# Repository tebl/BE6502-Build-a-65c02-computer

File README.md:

# BE6502 - Build a 6502 computer
[Ben Eater](https://eater.net/) has been a huge inspiration for many getting into building computers using basic electronic building blocks, his [videos](https://www.youtube.com/user/eaterbc) are truly excellent and it is no wonder he's often referred to as the Bob Ross of Breadboards! His latest project is [building a 6502 computer](https://eater.net/6502) on a breadboard, a video series that at this moment in time still has not concluded so this may not match whatever he does after part 7!

Personally, I am somewhat awful at getting things to work on breadboards - even when buying the good stuff from reputable electronics shops, so I usually just go directly to PCB instead. I've designed a few other amateur projects using the trusty old 6502-processor before, but this'll be the first one to be tackled with the more modern Western Designs CPU (W65C02) instead. His video series depends this specific brand of CPU, this is due to the way it is run using a slow and sometimes completely halted clock that wouldn't work the same on other brands. The older 6502 variants will more than likely loose their context, with the end result being a CPU doing unexpected things instead of running as the machine code would normally dictate. 

![LCD mounted](https://github.com/tebl/BE6502/raw/master/gallery/2019-12-06%2019.39.01.jpg
)

The BE6502 computer has a 39-pin backplane connector, like most of my other projects and these can be used to connect to an Arduino Mega as in the videos, a logic probe or even a separate larger backplane if you intend to build any more additional expansions for use with the computer. The picture above shows the SBC along with clock and Arduino Mega Shield. See *System modules* below for a listing of available modules, which are required at the various steps in the video series and any optional extras I felt like listing that would be compatible with the supplied boards.

Over time I may even add some short videos to show off the computer in action, but given that I have a voice suited for silent movies they'll probably just be videos of the computer blinking away by itself. As they become available, you'll find those on this [Youtube-playlist](https://www.youtube.com/playlist?list=PLOJSxpeHB9KTk9ptKCbEZnNEy9QRU02SS).

## Project status
The BE6502 computer is still in the prototyping stage and though I have studied the videos up to this point, at the time of writing that'd be everything up to and including part 7. See [TODO](https://github.com/tebl/BE6502/blob/master/TODO.md) for an overview of things I've yet to implement or want to change in the future!

Some of these details are likely to change as his original design by itself does not seem to reset reliably when using the 1 Mhz clock. At the moment I've got it fixed by using one of my own RC6502-modules in one of the backplane slots, details for this module can be found at https://github.com/tebl/RC6502-Apple-1-Replica/tree/master/RC6502%20Reset%20Circuit. If you'd like to build it up on a breadboard you can easily do that, I've installed pin headers as the front slot of my backplane to make it easier to do things like that. Alternatively you could program the Arduino Mega to do it for you!

### Errata
* [BE6502 SBC](https://github.com/tebl/BE6502/tree/master/BE6502%20SBC) revision A boards are missing a pull-up on the BE-pin - refer to this [picture](https://github.com/tebl/BE6502-Build-a-65c02-computer/raw/master/gallery/2020-02-16%2015.50.14-1.jpg) for a convenient spot to add one. This is resistor R18 in the current version of the schematic.
* [BE6502 Clock](https://github.com/tebl/BE6502-Build-a-65c02-computer/tree/master/BE6502%20Clock) module revision B had C8 shorted, refer to this [picture](https://github.com/tebl/BE6502-Build-a-65c02-computer/blob/master/gallery/Screenshot%202021-11-30%20194604.png) for how it should have looked (tracks have not been moved). In order to fix an existing PCB, cut off C8 and cut the trace directly below it. Installing new C8 (100nF) can be done on the back of the board, either across the short side of SW1 or between U2 pins 1 and 2.

## System modules
The following listed modules are available for use with the computer, where available I've also added an order URL to a shared project on PCBway for ease of ordering - click the module name to get more information as well as a complete list of components needed to build it (usually referred to as a BOM). Some modules have been marked with other computer names, these are other modules that I've found works directly and can be of interest when playing around with the BE6502-computer.

| Name      | Video series, parts 1-7 | Future expansions | Order  |
| --------- | ----------------------- | ----------------- | ------ |
| [Computer (SBC)](https://github.com/tebl/BE6502/tree/master/BE6502%20SBC) | required | | [PCBway](https://www.pcbway.com/project/shareproject/BE6502_Build_a_6502_computer__SBC_module_revision_A_.html?inviteid=88707) |
| [Adjustable and manual clock](https://github.com/tebl/BE6502/tree/master/BE6502%20Clock) | required | | [PCBway](https://www.pcbway.com/project/shareproject/BE6502_Build_a_6502_computer__Clock_module_revision_A_.html?inviteid=88707) |
| [Arduino Mega Shield and Backplane ](https://github.com/tebl/BE6502/tree/master/BE6502%20Mega%20Adapter) | required | | [PCBway](https://www.pcbway.com/project/shareproject/BE6502_Build_a_6502_computer__Arduino__and_backplane_module_.html?inviteid=88707) |
| [RC6502 Backplane](https://github.com/tebl/RC6502-Apple-1-Replica/tree/master/RC6502%20Backplane) |  | optional | [PCBWay](https://www.pcbway.com/project/shareproject/RC6502_Apple_1_Replica__Backplane_module_revision_A_.html?inviteid=88707) |
| [RC6502 Prototyping module](https://github.com/tebl/RC6502-Apple-1-Replica/tree/master/RC6502%20Prototyping) | | optional | [PCBWay](https://www.pcbway.com/project/shareproject/RC6502_Apple_1_Replica__Module_prototyping_board_.html?inviteid=88707) |

If you would like to have a copy of one or more modules (usually 5$ per module), consider using the order links in order to support the development of these boards while doing so. You can alternatively zip up the contents of the export directory for each module and give that to your favourite PCB fabrication plant instead if you want to, but note that the files online here may be newer and have changes made to them that may not have been tested yet (the order link above will point to my last tested version).

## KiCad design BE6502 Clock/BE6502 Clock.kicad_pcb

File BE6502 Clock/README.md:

[Ben Eater](https://eater.net/) has been a huge inspiration for many getting into building computers using basic electronic building blocks, his [videos](https://www.youtube.com/user/eaterbc) are truly excellent and it is no wonder he's often referred to as the Bob Ross of Breadboards! His latest project is [building a 6502 computer](https://eater.net/6502) on a breadboard, a video series that I'm sure will also inspire a lot of new users to the art of building stuff with the 6502! Check out the main [README](https://github.com/tebl/BE6502) for an overview of all the modules available to the BE6502 computer.

## Clock Module
Ben Eater has used the clock module from his 8 bit computer build with this project as well, this module is my implementation with only a few tweaks to the design. The main change apart from the whole PCB-design is that it has a slightly reduced chip-count, this was done by replacing the single used OR-gate with three NAND-gates instead (a little NAND-logic exercise).

Like the original breadboard version, you have a manual clock that allows you to clock in manual clock-pulses by pushing the button - the 555 in this case is used for debouncing (mechanical switches are not actually all that consistent). An adjustable slow clock is also available, here the 555 is used as a vibrator and will generate clock pulses with a frequency that is adjustable via the potentiometer. The final 555 allows for a clean transition between the two clocks so you can switch between the two without any erratic bahavior.

# Schematic
The supplied KiCad files should be sufficient as both a schematic and as a starting point for ordering PCBs (basically you could just zip the contents of the export folder and upload that on a fabrication site), the schematic is also available in [PDF-format](https://github.com/tebl/BE6502/raw/master/BE6502%20Clock/export/BE6502%20Clock.pdf) so that you can refer to it while troubleshooting. You could even print it out and hang it on your office wall, excellent conversation starter at any technology-oriented business worth working at (or so I keep telling myself)!

# BOM
This is the part list as it stands now, most should be easy to get a hold of from your local electronic component shop though you might have to consider other sources depending on the quality of yourlocal vendor.

Some vendors will have the same ICs in different form factors, the ones you want will often be specified as being in the form of a DIP/PDIP package. Usually you'll want sockets for each of the ICs as well, a bag of assorted sockets should be easily available without setting you back more than a couple bucks. With the sockets in place, you don't need to dread having to remove an IC later, this leads to easier fault finding and you can easily "borrow" them for other projects later! For the pin headers; if you can't find the exact pin count, just buy the longer 40 pin versions and snip off the parts you don't need.

| Reference    | Item                                  | Count |
| ------------ | ------------------------------------- | ----- |
| PCB          | Fabricate yourself using Gerber files ([order](https://www.pcbway.com/project/shareproject/BE6502_Build_a_6502_computer__Clock_module_revision_A_.html?inviteid=88707)) |     1 |
| C1.C2,C5     | 10nF ceramic capacitor                |     3 |
| C3.C4,C7     | 100nF ceramic capacitor               |     3 |
| C6           | 1uF electrolytic capacitor (2.5mm)    |     1 |
| D1           | 5mm LED                               |     1 |
| R1-R3,R5-R6  | 1k ohm resistor                       |     5 |
| R4           | 1M ohm resistor                       |     1 |
| R7           | 220 ohm resistor                      |     1 |
| RV1          | Bourns 3296W 1M ohm potentiometer     |     1 |
| U1-U3        | LM555, NE555 or equivalent (DIP-8)    |     3 |
| U4           | 74HC00 (DIP-14) *                     |     1 |
| U5           | 74HC08 (DIP-14) *                     |     1 |
| SW1          | Momentary push button                 |     1 |
| SW2          | 6pin 8.5mm x 8.5mm latching switch    |     1 |
| J1           | 4p straight pin header **             |     1 |

\*) HC-series chips have been specified as that is what Ben Eater used in his Build a 6502 computer series, but can also be HCT-series depending on what you have access to. For more information on the various logic families, see the [6502 Primer on the topic of logic families](http://wilsonminesco.com/6502primer/LogicFamilies.html).

\**) You can use a female right-angle pin header and match it directly to the BE6502 SBC with some careful adjustments, but I recommend using some female to female dupont leads instead as the connector is a bit too loose when not mounting boards on a backing plate.

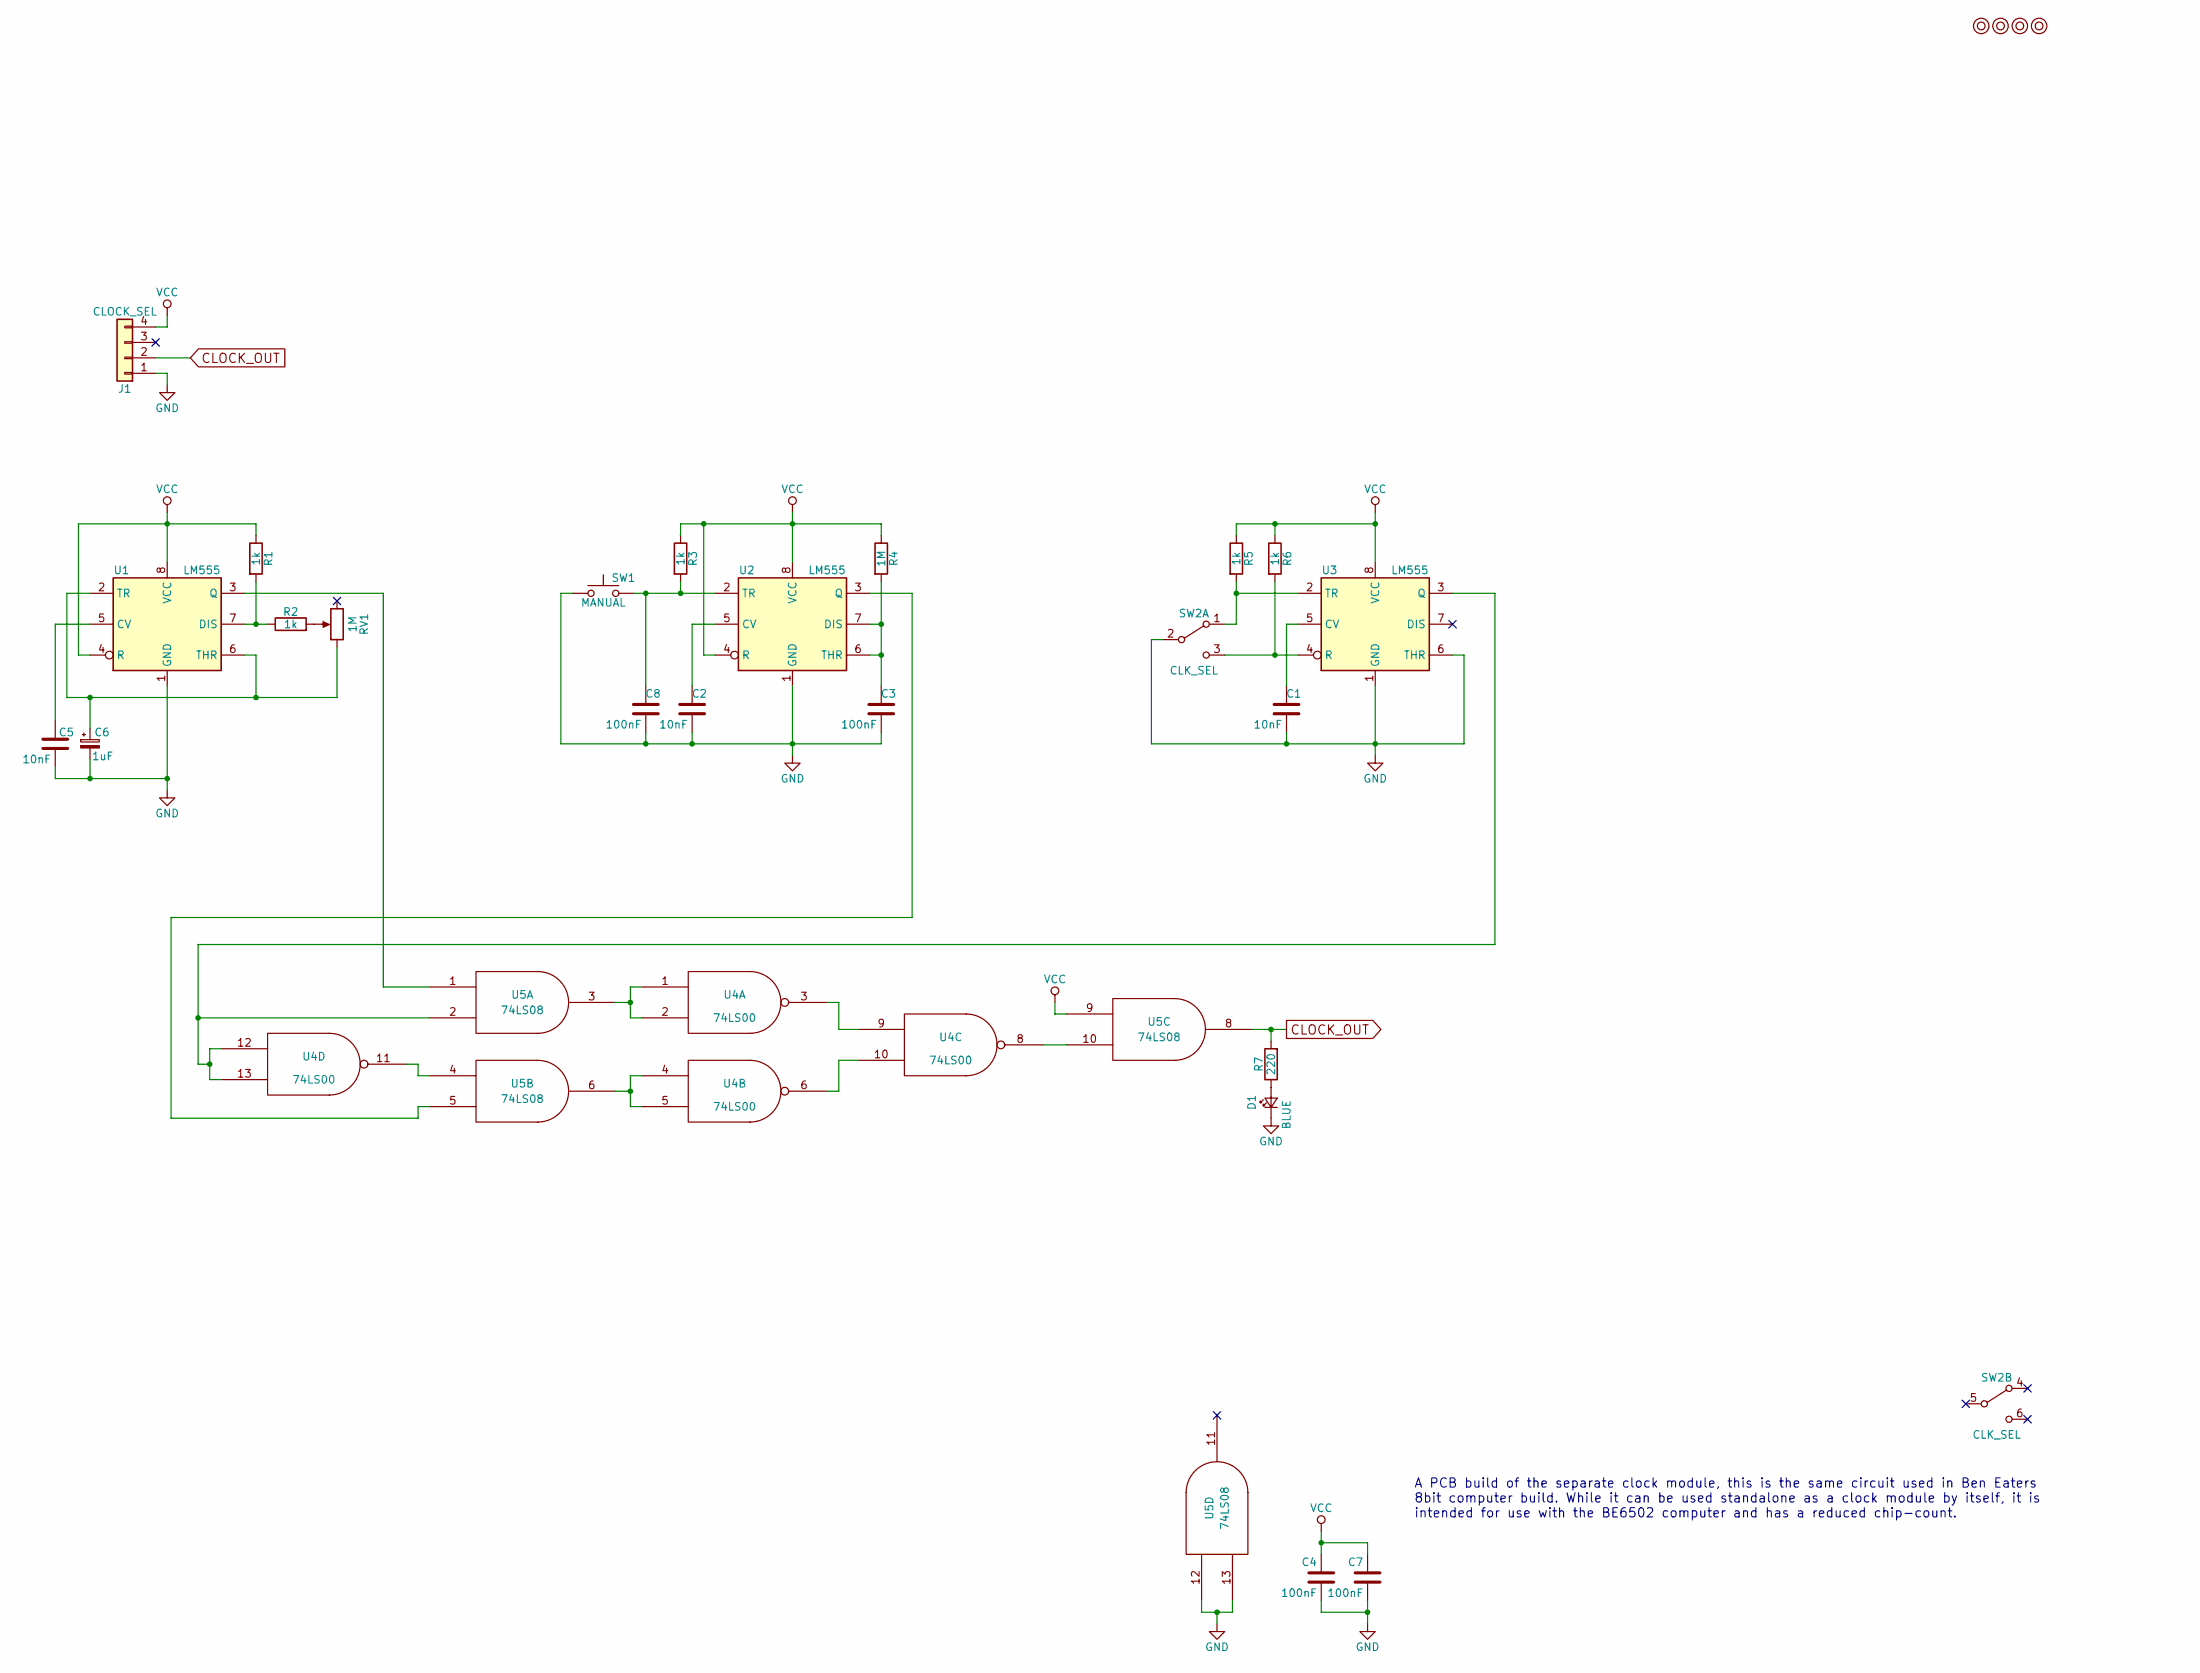
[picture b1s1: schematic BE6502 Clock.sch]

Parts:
C1, C2, C5: 10nF; C_Disc_D4.7mm_W2.5mm_P5.00mm
C3, C4, C7, C8: 100nF; C_Disc_D4.7mm_W2.5mm_P5.00mm
C6: 1uF; CP_Radial_D4.0mm_P2.00mm
D1: BLUE; LED_D5.0mm
J1: CLOCK_SEL; Pin_Header_Angled_1x04_Pitch2.54mm
M1, M2, M3, M4: Mounting; 1pin
R1, R2, R3, R5, R6: 1k; R_Axial_DIN0207_L6.3mm_D2.5mm_P10.16mm_Horizontal
R4: 1M; R_Axial_DIN0207_L6.3mm_D2.5mm_P10.16mm_Horizontal
R7: 220; R_Axial_DIN0207_L6.3mm_D2.5mm_P10.16mm_Horizontal
RV1: 1M; Potentiometer_Trimmer_Bourns_3296W
SW1: MANUAL; SW_PUSH_6mm
SW2: CLK_SEL; dpdt_switch
U1, U2, U3: LM555; DIP-8_W7.62mm_Socket_LongPads
U4: 74LS00; DIP-14_W7.62mm_Socket_LongPads
U5: 74LS08; DIP-14_W7.62mm_Socket_LongPads

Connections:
CLOCK_OUT: J1.2, R7.2, U5.8
GND: C1.2, C2.2, C3.2, C4.2, C5.2, C6.2, C7.2, C8.2, D1.1 (K), J1.1, SW1.1, SW2.2 (B), U1.1 (GND), U2.1 (GND), U3.1 (GND), U3.6 (THR), U4.7 (GND), U5.7 (GND), U5.12, U5.13
unnamed: C1.1, U3.5 (CV)
unnamed: C2.1, U2.5 (CV)
unnamed: C3.1, R4.2, U2.6 (THR), U2.7 (DIS)
unnamed: C5.1, U1.5 (CV)
unnamed: C6.1, RV1.1, U1.2 (TR), U1.6 (THR)
unnamed: C8.1, R3.2, SW1.2, U2.2 (TR)
unnamed: D1.2 (A), R7.1
unnamed: R1.2, R2.1, U1.7 (DIS)
unnamed: R2.2, RV1.2
unnamed: R5.2, SW2.1 (A), U3.2 (TR)
unnamed: R6.2, SW2.3 (C), U3.4 (R)
unnamed: U1.3 (Q), U5.1
unnamed: U2.3 (Q), U5.5
unnamed: U3.3 (Q), U4.12, U4.13, U5.2
unnamed: U4.1, U4.2, U5.3
unnamed: U4.3, U4.9
unnamed: U4.4, U4.5, U5.6
unnamed: U4.8, U5.10
unnamed: U4.6, U4.10
unnamed: U4.11, U5.4
VCC: C4.1, C7.1, J1.4, R1.1, R3.1, R4.1, R5.1, R6.1, U1.4 (R), U1.8 (VCC), U2.4 (R), U2.8 (VCC), U3.8 (VCC), U4.14 (VCC), U5.9, U5.14 (VCC)

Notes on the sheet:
A PCB build of the separate clock module, this is the same circuit used in Ben Eaters 8bit computer build. While it can be used standalone as a clock module by itself, it is intended for use with the BE6502 computer and has a reduced chip-count.

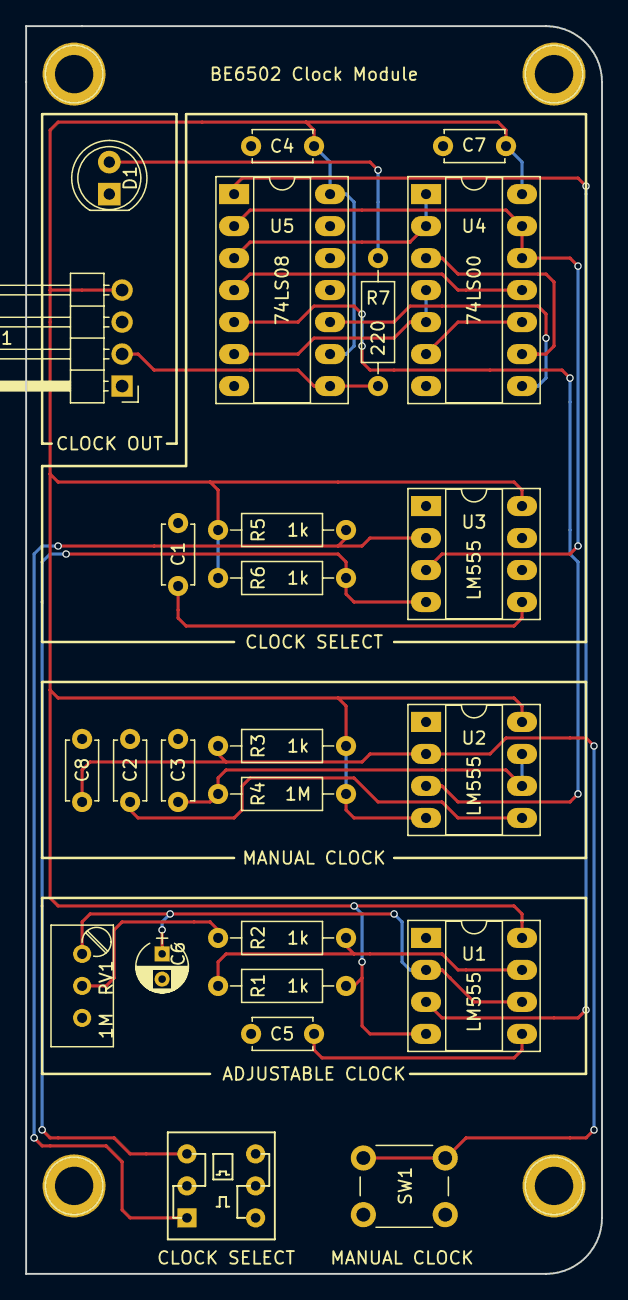
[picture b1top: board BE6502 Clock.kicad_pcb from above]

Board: 2 copper layers, 45.7 x 99.1 mm, 29 parts (0 on the bottom side), 23 nets.

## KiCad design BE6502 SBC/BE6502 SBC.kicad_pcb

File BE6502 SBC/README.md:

# BE6502
[Ben Eater](https://eater.net/) has been a huge inspiration for many getting into building computers using basic electronic building blocks, his [videos](https://www.youtube.com/user/eaterbc) are truly excellent and it is no wonder he's often referred to as the Bob Ross of Breadboards! His latest project is [building a 6502 computer](https://eater.net/6502) on a breadboard, a video series that I'm sure will also inspire a lot of new users to the art of building stuff with the 6502! Check out the main [README](https://github.com/tebl/BE6502) for an overview of all the modules available to the BE6502 computer.

## Computer (SBC-module)
This module specifically contains all of the modules that makes the BE6502 an actual computer, it has the CPU, RAM, ROM and a way of interacting with the world using the VIA-chip. Also described as an SBC-module which means that it is a *Single Board Computer* though I'm certainly a fan of building more things around it, I just look at it has giving the computer more tricks that it can use to both entertain and educate us at the same time.

The picture above shows an assembled and currently running version of the SBC-module (without LCD attached), here I used a female pin header so that the clock module could be slotted directly into place alongside it. I did however change this to use dupont-cables later, this was because the boards separated too easily without having a plate to screw everything into at the moment

As you can see from the big shiny thing, I've also got the 1 Mhz oscillator installed as it is listed in Ben Eaters design though it is not connected by default so that the adjustable or manual clock can be used instead - to enable the 1 Mhz clock you'll need to install a jumper as shown below.

I did however have some issues running the CPU reliably at this speed, this is due to the reset circuit specified not being suitable for use at anything other than very low speeds. While we're probably waiting for part 8 of the video series to fix this issue, you can build one yourself on a breadboard with just about the same parts seen earlier in the series.

The hardware solution I'm using is a somewhat simplified version of the one at [RC6502 Reset Circuit](https://github.com/tebl/RC6502-Apple-1-Replica/tree/master/RC6502%20Reset%20Circuit), this is mainly by leaving out the oscillator (since we've already got one) and the 74LS74. For masters of the Commodore 64 the circuit will seem familiar, this is because it's the one originally used on its boards! Alternatively as a software solution, the Arduino Mega can also be used to perform this task - this is done by holding down the first switch (since revision B of the Mega Adapter) or by typing in reset via the serial interface.

## Jumpers
| Reference | Position | Description                                        |
| --------- | -------- | -------------------------------------------------- |
| LCD_EN    | 1-2      | Enable LCD                                         |
|           | 2-3 *    | Disable LCD without physically removing it         |
| LED_EN    | o-o *    | Jumpered to enable port B LEDs                     |
| CLOCK_SEL | 1   **   | VCC                                                |
|           | 2-3 **   | Jumper to enable 1 Mhz clock                       |
|           | 4   **   | GND                                                |

*) Marks the default jumpered positions when performing tasks associated with the first parts of the video series. Later, when the LCD is introduced, these will have to be changed.

**) CLOCK_SEL is also used as a connector when connecting the clock module, the pins are made to directly match the 4 positions on both modules. Pins 2-3 should only be jumpered when using 1Mhz clock, but you can also use pins 1 and 4 when powering other circuits. 

# Schematic
The supplied KiCad files should be sufficient as both a schematic and as a starting point for ordering PCBs (basically you could just zip the contents of the export folder and upload that on a fabrication site), the schematic is also available in [PDF-format](https://github.com/tebl/BE6502/raw/master/BE6502%20SBC/export/BE6502%20SBC.pdf) so that you can refer to it while troubleshooting. You could even print it out and hang it on your office wall, excellent conversation starter at any technology-oriented business worth working at (or so I keep telling myself)!

# BOM
This is the part list as it stands now, most should be easy to get a hold of from your local electronic component shop though you might have to consider other sources as that would depend on the quality of your local vendor.

Some vendors will have the same ICs in different form factors, the ones you want will often be specified as being in the form of a DIP/PDIP package. Usually you'll want sockets for each of the ICs as well, a bag of assorted sockets should be easily available without setting you back more than a couple bucks. With the sockets in place, you don't need to dread having to remove an IC later, this leads to easier fault finding and you can easily "borrow" them for other projects later! For the pin headers; you probably won't find the exact pin count as most are meant to be cut down to size, so just buy the 40 pin versions and snip off the parts you don't need!

| Reference    | Item                                  | Count |
| ------------ | ------------------------------------- | ----- |
| PCB          | Fabricate yourself using Gerber files |     1 |
| C1-C6        | 100nF ceramic capacitor               |     6 |
| D1-D8        | 5mm LED diode, green or red color     |     8 |
| J1           | 39p right angle pin header            |     1 |
| J2           | 4p right angle pin header             |     1 |
| JP1          | 2p straight pin header                |     1 |
| JP3          | 3p straight pin header                |     1 |
| J3           | 2.1mm x 5.5mm barrel plug             |     1 |
| JP1          | Single row, 2p straight pin header    |     2 |
| R1-R3,R18*   | 3k3 (3300) ohm resistor               |     4 |
| R4-R9        | 1k ohm resistor                       |     6 |
| R10-R17      | 220 ohm resistor                      |     8 |
| U1           | W65C02 DIP-40                         |     1 |
| U2           | 62256 Static RAM (DIP-28)             |     1 |
| U3           | 28C256 EEPROM (DIP-28)                |     1 |
| U4           | W65C22S DIP-40                        |     1 |
| U5           | 74HC00 DIP                            |     1 |
| U6           | RC1602A, 16x2 character LCD           |     1 |
| SW1-SW6      | Momentary push button                 |     6 |
| X1           | 1.000Mhz TTL Oscillator, (DIP-14)     |     1 |
|              | Jumpers for settings (CAP headers)    |     3 |

*) R18 was added to SBC revision B boards as I had forgotten to add the pull-up for the BE-line, causing instability on the boards due to it floating around. Refer to this [picture](https://github.com/tebl/BE6502-Build-a-65c02-computer/raw/master/gallery/2020-02-16%2015.50.14-1.jpg) for a convenient spot to add it to revision A boards.

When constructing the board I recommend using 60/40 solder as the lead-free is more trouble than it's worth for hobby use, take your time with it and try to build up the board starting with the lowest components before moving on to the larger pieces. The LCD will be mounted on top of other components, so check that nothing shorts on the underside and unless you're 100% sure about the construction and my design - install some female header pins on it so that you can easily remove it while troubleshooting the circuit underneath!

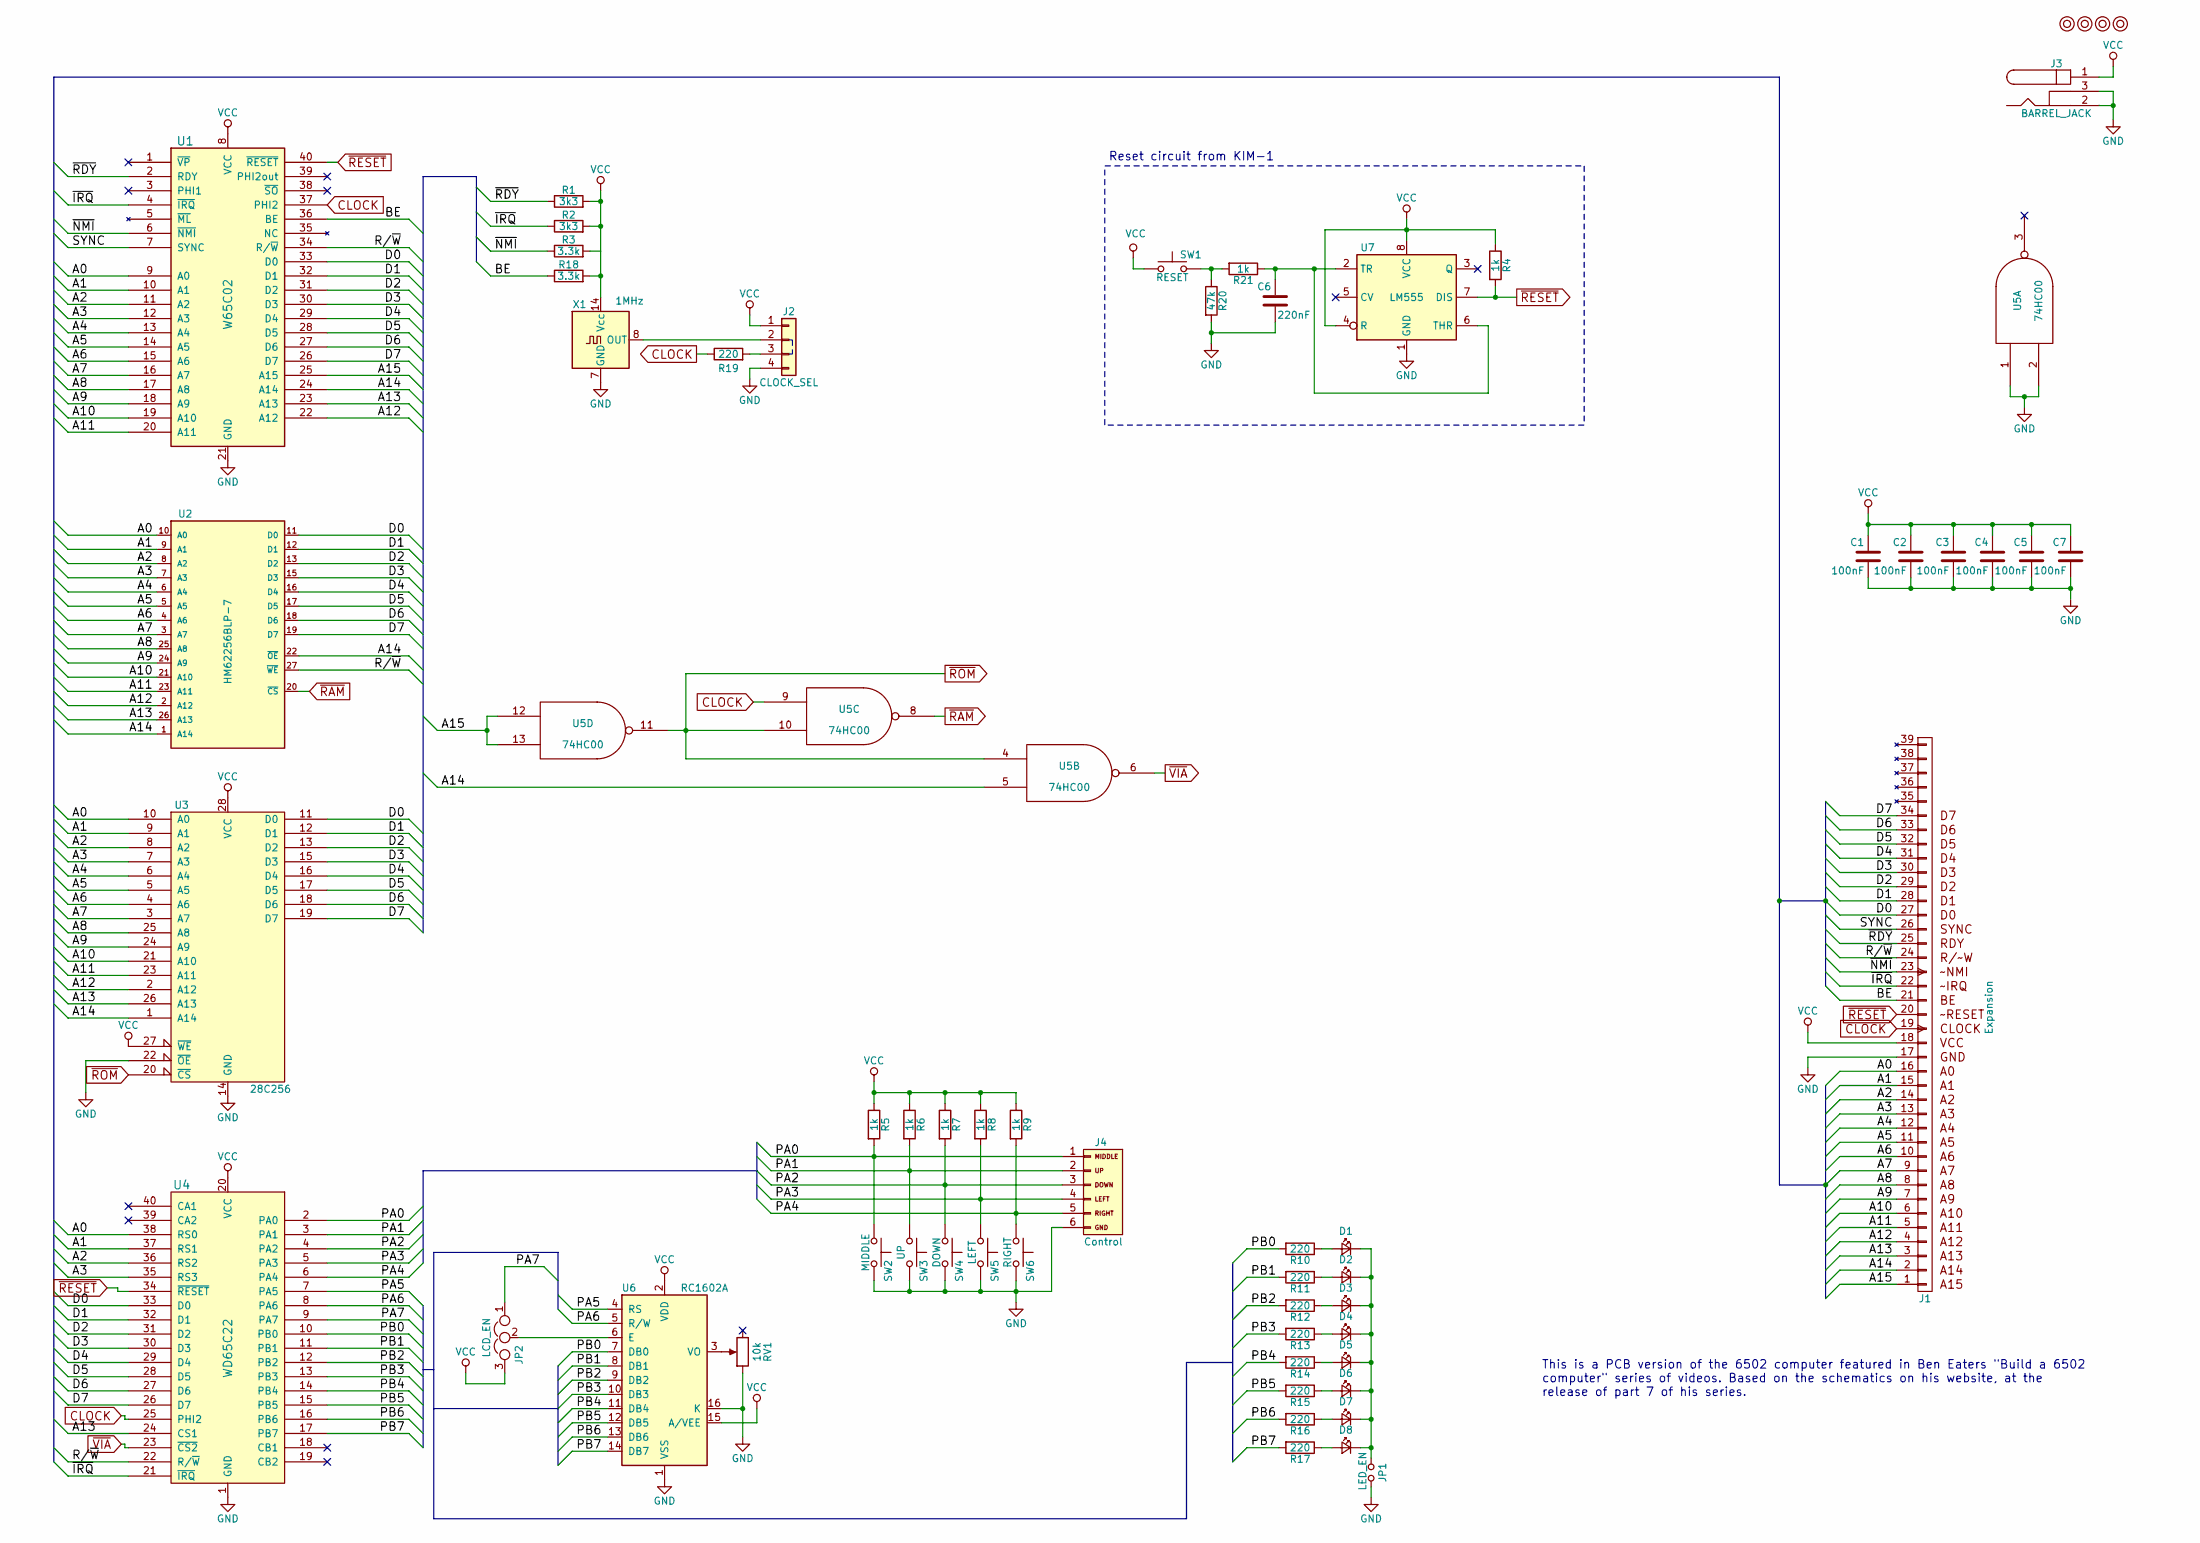
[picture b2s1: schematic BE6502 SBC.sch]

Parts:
C1, C2, C3, C4, C5, C7: 100nF; C_Disc_D4.7mm_W2.5mm_P5.00mm
C6: 220nF; C_Disc_D4.7mm_W2.5mm_P5.00mm
D1, D2, D3, D4, D5, D6, D7, D8: LED; LED_D5.0mm
J1: Expansion; Pin_Header_Angled_1x39_Pitch2.54mm
J2: CLOCK_SEL; Pin_Header_Angled_1x04_Pitch2.54mm
J3: BARREL_JACK
J4: Control; Pin_Header_Angled_1x06_Pitch2.54mm
JP1: LED_EN; Pin_Header_Straight_1x02_Pitch2.54mm
JP2: LCD_EN; Pin_Header_Straight_1x03_Pitch2.54mm
M1, M2, M3, M4: Mounting; 1pin
R1, R2: 3k3; R_Axial_DIN0207_L6.3mm_D2.5mm_P10.16mm_Horizontal
R3, R18: 3.3k; R_Axial_DIN0207_L6.3mm_D2.5mm_P10.16mm_Horizontal
R4, R5, R6, R7, R8, R9, R21: 1k; R_Axial_DIN0207_L6.3mm_D2.5mm_P10.16mm_Horizontal
R10, R11, R12, R13, R14, R15, R16, R17, R19: 220; R_Axial_DIN0207_L6.3mm_D2.5mm_P10.16mm_Horizontal
R20: 47k; R_Axial_DIN0207_L6.3mm_D2.5mm_P10.16mm_Horizontal
RV1: 10k; Potentiometer_Trimmer_Bourns_3296W
SW1: RESET; SW_PUSH_6mm
SW2: MIDDLE; SW_PUSH_6mm
SW3: UP; SW_PUSH_6mm
SW4: DOWN; SW_PUSH_6mm
SW5: LEFT; SW_PUSH_6mm
SW6: RIGHT; SW_PUSH_6mm
U1: W65C02; DIP-40_W15.24mm_Socket_LongPads
U2: HM62256BLP-7; DIP-28_W15.24mm_Socket_LongPads
U3: 28C256; DIP-28_W15.24mm_Socket_LongPads
U4: WD65C22; DIP-40_W15.24mm_Socket_LongPads
U5: 74HC00; DIP-14_W7.62mm_Socket_LongPads
U6: RC1602A; WC1602A
U7: LM555; DIP-8_W7.62mm_Socket_LongPads
X1: 1MHz; Oscillator_DIP-14

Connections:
/A0: J1.16 (A0), U1.9 (A0), U2.10 (A0), U3.10 (A0), U4.38 (RS0)
/A1: J1.15 (A1), U1.10 (A1), U2.9 (A1), U3.9 (A1), U4.37 (RS1)
/A2: J1.14 (A2), U1.11 (A2), U2.8 (A2), U3.8 (A2), U4.36 (RS2)
/A3: J1.13 (A3), U1.12 (A3), U2.7 (A3), U3.7 (A3), U4.35 (RS3)
/A4: J1.12 (A4), U1.13 (A4), U2.6 (A4), U3.6 (A4)
/A5: J1.11 (A5), U1.14 (A5), U2.5 (A5), U3.5 (A5)
/A6: J1.10 (A6), U1.15 (A6), U2.4 (A6), U3.4 (A6)
/A7: J1.9 (A7), U1.16 (A7), U2.3 (A7), U3.3 (A7)
/A8: J1.8 (A8), U1.17 (A8), U2.25 (A8), U3.25 (A8)
/A9: J1.7 (A9), U1.18 (A9), U2.24 (A9), U3.24 (A9)
/A10: J1.6 (A10), U1.19 (A10), U2.21 (A10), U3.21 (A10)
/A11: J1.5 (A11), U1.20 (A11), U2.23 (A11), U3.23 (A11)
/A12: J1.4 (A12), U1.22 (A12), U2.2 (A12), U3.2 (A12)
/A13: J1.3 (A13), U1.23 (A13), U2.26 (A13), U3.26 (A13), U4.24 (CS1)
/A14: J1.2 (A14), U1.24 (A14), U2.1 (A14), U2.22 (~OE), U3.1 (A14), U5.5
/A15: J1.1 (A15), U1.25 (A15), U5.12, U5.13
/BE: J1.21 (BE), R18.1, U1.36 (BE)
/D0: J1.27 (D0), U1.33 (D0), U2.11 (D0), U3.11 (D0), U4.33 (D0)
/D1: J1.28 (D1), U1.32 (D1), U2.12 (D1), U3.12 (D1), U4.32 (D1)
/D2: J1.29 (D2), U1.31 (D2), U2.13 (D2), U3.13 (D2), U4.31 (D2)
/D3: J1.30 (D3), U1.30 (D3), U2.15 (D3), U3.15 (D3), U4.30 (D3)
/D4: J1.31 (D4), U1.29 (D4), U2.16 (D4), U3.16 (D4), U4.29 (D4)
/D5: J1.32 (D5), U1.28 (D5), U2.17 (D5), U3.17 (D5), U4.28 (D5)
/D6: J1.33 (D6), U1.27 (D6), U2.18 (D6), U3.18 (D6), U4.27 (D6)
/D7: J1.34 (D7), U1.26 (D7), U2.19 (D7), U3.19 (D7), U4.26 (D7)
/PA0: J4.1 (MIDDLE), R5.2, SW2.1, U4.2 (PA0)
/PA1: J4.2 (UP), R6.2, SW3.1, U4.3 (PA1)
/PA2: J4.3 (DOWN), R7.2, SW4.1, U4.4 (PA2)
/PA3: J4.4 (LEFT), R8.2, SW5.1, U4.5 (PA3)
/PA4: J4.5 (RIGHT), R9.2, SW6.1, U4.6 (PA4)
/PA5: U4.7 (PA5), U6.4 (RS)
/PA6: U4.8 (PA6), U6.5 (R/W)
/PA7: JP2.1, U4.9 (PA7)
/PB0: R10.2, U4.10 (PB0), U6.7 (DB0)
/PB1: R11.2, U4.11 (PB1), U6.8 (DB1)
/PB2: R12.2, U4.12 (PB2), U6.9 (DB2)
/PB3: R13.2, U4.13 (PB3), U6.10 (DB3)
/PB4: R14.2, U4.14 (PB4), U6.11 (DB4)
/PB5: R15.2, U4.15 (PB5), U6.12 (DB5)
/PB6: R16.2, U4.16 (PB6), U6.13 (DB6)
/PB7: R17.2, U4.17 (PB7), U6.14 (DB7)
/R/~W: J1.24 (RW), U1.34 (R/~W), U2.27 (~WE), U4.22 (R/~W)
/SYNC: J1.26 (SYNC), U1.7 (SYNC)
/~IRQ: J1.22 (IRQ), R2.1, U1.4 (~IRQ), U4.21 (~IRQ)
/~NMI: J1.23 (PHI1), R3.1, U1.6 (~NMI)
/~RDY: J1.25 (READY), R1.1, U1.2 (RDY)
CLOCK: J1.19 (PHI2), R19.1, U1.37 (PHI2), U4.25 (PHI2), U5.9
GND: C1.2, C2.2, C3.2, C4.2, C5.2, C6.2, C7.2, J1.17, J2.4, J3.2, J3.3, J4.6 (GND), JP1.1, R20.2, RV1.1, SW2.2, SW3.2, SW4.2, SW5.2, SW6.2, U1.21 (GND), U2.14 (GND), U3.14 (GND), U3.22 (~OE), U4.1 (GND), U5.1, U5.2, U5.7 (GND), U6.1 (VSS), U6.16 (K), U7.1 (GND), X1.7 (GND)
unnamed: C6.1, R21.1, U7.2 (TR), U7.6 (THR)
unnamed: D1.1 (K), D2.1 (K), D3.1 (K), D4.1 (K), D5.1 (K), D6.1 (K), D7.1 (K), D8.1 (K), JP1.2
unnamed: D1.2 (A), R10.1
unnamed: D2.2 (A), R11.1
unnamed: D3.2 (A), R12.1
unnamed: D4.2 (A), R13.1
unnamed: D5.2 (A), R14.1
unnamed: D6.2 (A), R15.1
unnamed: D7.2 (A), R16.1
unnamed: D8.2 (A), R17.1
unnamed: J2.2, X1.8 (OUT)
unnamed: J2.3, R19.2
unnamed: JP2.2, U6.6 (E)
unnamed: R20.1, R21.2, SW1.2
unnamed: RV1.2, U6.3 (VO)
VCC: C1.1, C2.1, C3.1, C4.1, C5.1, C7.1, J1.18, J2.1, J3.1, JP2.3, R1.2, R2.2, R3.2, R4.1, R5.1, R6.1, R7.1, R8.1, R9.1, R18.2, SW1.1, U1.8 (VCC), U2.28 (VCC), U3.27 (~WE), U3.28 (VCC), U4.20 (VCC), U5.14 (VCC), U6.2 (VDD), U6.15 (A/VEE), U7.4 (R), U7.8 (VCC), X1.14 (Vcc)
~RAM: U2.20 (~CS), U5.8
~RESET: J1.20 (RESET), R4.2, U1.40 (~RESET), U4.34 (~RESET), U7.7 (DIS)
~ROM: U3.20 (~CS), U5.4, U5.10, U5.11
~VIA: U4.23 (~CS2), U5.6

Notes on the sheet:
This is a PCB version of the 6502 computer featured in Ben Eaters "Build a 6502 computer" series of videos. Based on the schematics on his website, at the release of part 7 of his series.
Reset circuit from KIM-1

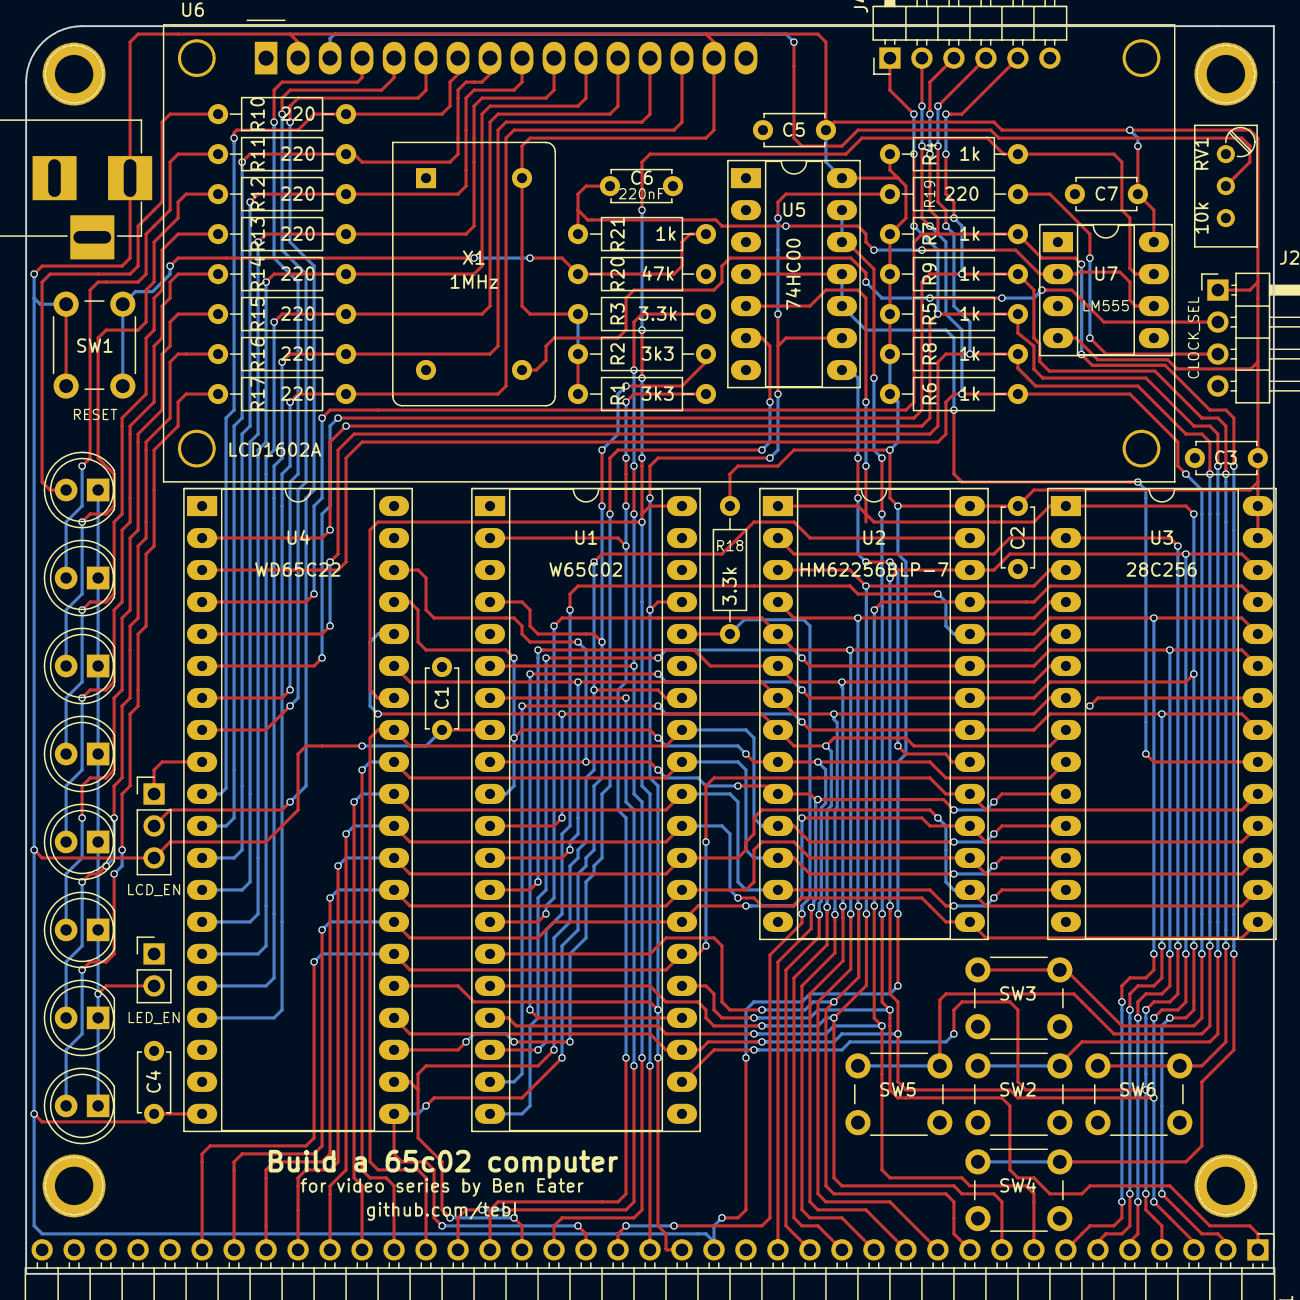
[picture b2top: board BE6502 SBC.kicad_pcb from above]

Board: 2 copper layers, 99.1 x 99.1 mm, 61 parts (0 on the bottom side), 68 nets.
